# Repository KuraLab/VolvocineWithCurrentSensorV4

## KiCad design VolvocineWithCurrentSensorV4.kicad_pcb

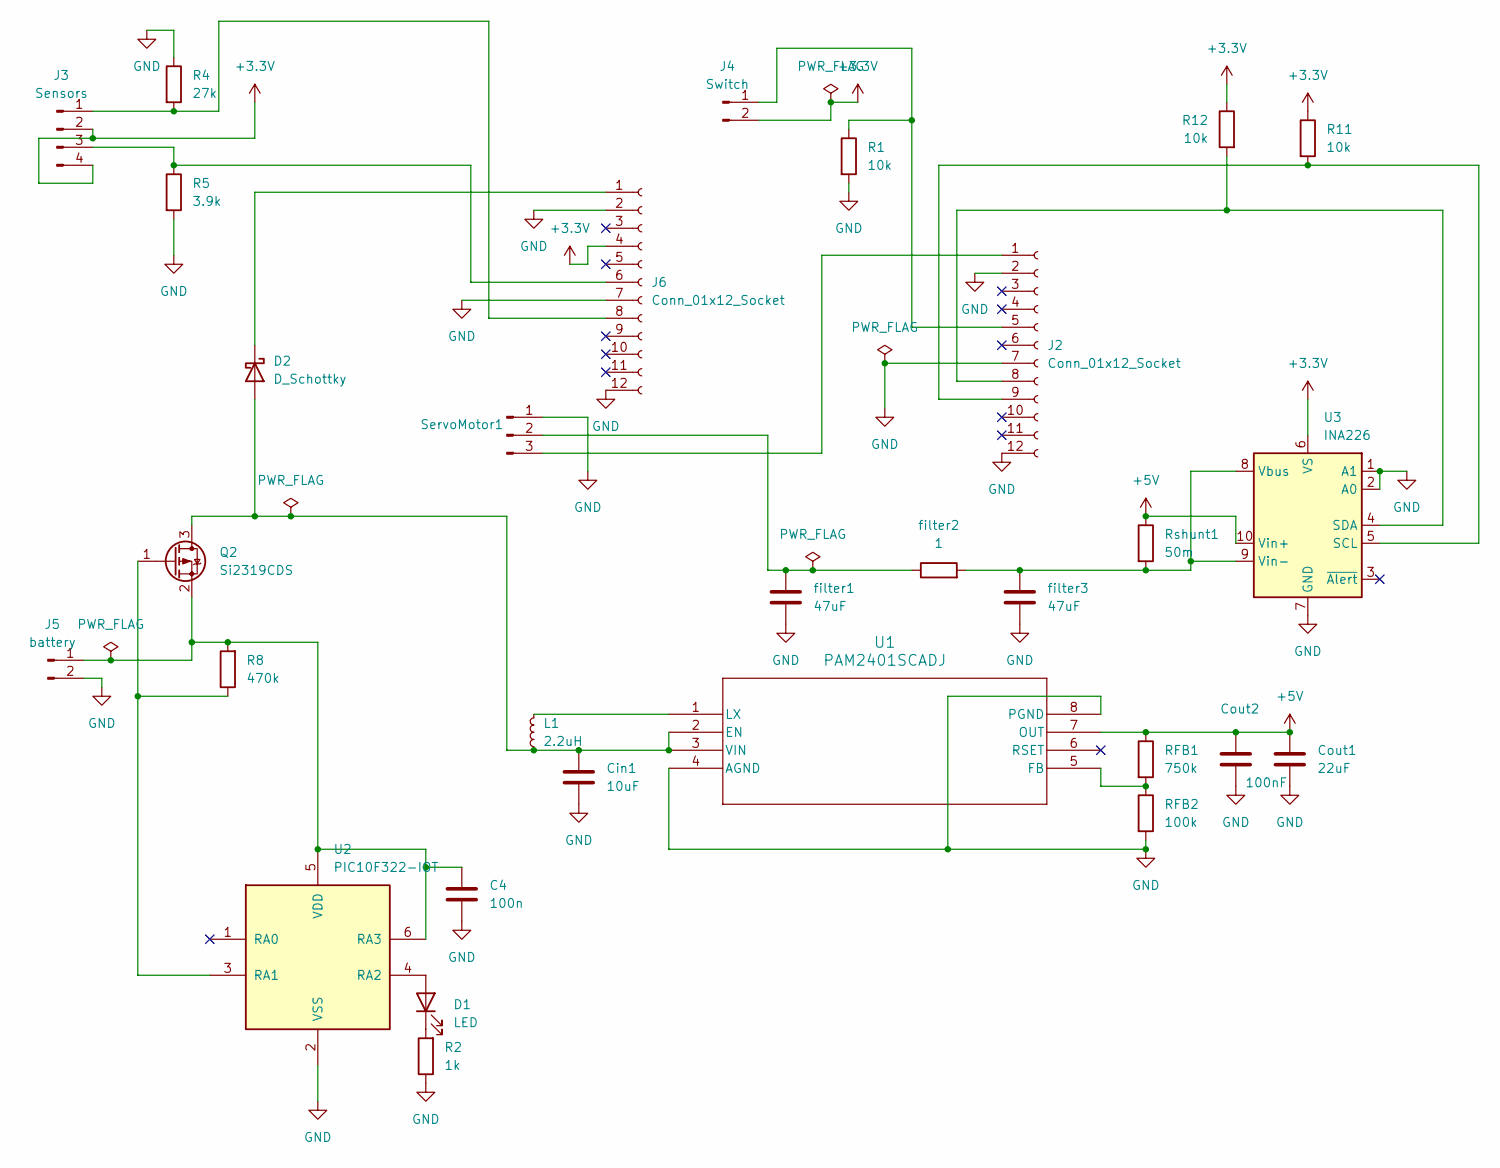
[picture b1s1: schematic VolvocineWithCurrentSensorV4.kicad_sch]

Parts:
C4: 100n; C_0603_1608Metric_Pad1.08x0.95mm_HandSolder
Cin1: 10uF; C_0603_1608Metric_Pad1.08x0.95mm_HandSolder
Cout1: 22uF; C_1206_3216Metric_Pad1.33x1.80mm_HandSolder
Cout2: 100nF; C_0603_1608Metric_Pad1.08x0.95mm_HandSolder
D1: LED; LED_0603_1608Metric_Pad1.05x0.95mm_HandSolder
D2: D_Schottky; D_SOD-128
J2, J6: Conn_01x12_Socket; PinSocket_1x12_P2.54mm_Vertical
J3: Sensors; PinHeader_1x04_P2.54mm_Vertical
J4: Switch; PinHeader_1x02_P2.54mm_Vertical
J5: battery; PinHeader_1x02_P2.54mm_Vertical
L1: 2.2uH; L_1008_2520Metric_Pad1.43x2.20mm_HandSolder
Q2: Si2319CDS; SOT-23
R1, R11, R12: 10k; R_0603_1608Metric_Pad0.98x0.95mm_HandSolder
R2: 1k; R_0603_1608Metric_Pad0.98x0.95mm_HandSolder
R4: 27k; R_0603_1608Metric_Pad0.98x0.95mm_HandSolder
R5: 3.9k; R_0603_1608Metric_Pad0.98x0.95mm_HandSolder
R8: 470k; R_0603_1608Metric_Pad0.98x0.95mm_HandSolder
RFB1: 750k; R_0603_1608Metric_Pad0.98x0.95mm_HandSolder
RFB2: 100k; R_0603_1608Metric_Pad0.98x0.95mm_HandSolder
Rshunt1: 50m; R_1206_3216Metric_Pad1.30x1.75mm_HandSolder
ServoMotor1: PinHeader_1x03_P2.54mm_Vertical
U1: PAM2401SCADJ; MSOP-8_3x3mm_P0.65mm
U2: PIC10F322-IOT; SOT-23-6
U3: INA226; VSSOP-10_3x3mm_P0.5mm
filter1, filter3: 47uF; C_1206_3216Metric_Pad1.33x1.80mm_HandSolder
filter2: 1; R_0603_1608Metric_Pad0.98x0.95mm_HandSolder

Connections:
+3.3V: J3.2, J3.4, J4.2, J6.4, R11.1, R12.1, U3.6 (VS)
+5V: Cout1.1, Cout2.1, RFB1.1, Rshunt1.1, U1.7 (OUT), U3.10 (Vin+)
GND: C4.2, Cin1.2, Cout1.2, Cout2.2, J2.2, J2.7, J2.12, J5.2, J6.2, J6.7, J6.12, R1.2, R2.1, R4.1, R5.2, RFB2.2, ServoMotor1.1, U1.4 (AGND), U1.8 (PGND), U2.2 (VSS), U3.1 (A1), U3.2 (A0), U3.7 (GND), filter1.2, filter3.2; also elsewhere on the board
unnamed: D1.2 (A), U2.4 (RA2)
unnamed: D1.1 (K), R2.2
unnamed: Cin1.1, D2.2 (A), L1.1, Q2.3 (D), U1.2 (EN), U1.3 (VIN)
unnamed: D2.1 (K), J6.1
unnamed 7: J2.1, ServoMotor1.3; also elsewhere on the board
unnamed: J2.5, J4.1, R1.1
unnamed: J2.8, R12.2, U3.4 (SDA)
unnamed: J2.9, R11.2, U3.5 (SCL)
unnamed: J3.1, J6.8, R4.2
unnamed: J3.3, J6.6, R5.1
unnamed: C4.1, J5.1, Q2.2 (S), R8.2, U2.5 (VDD), U2.6 (RA3)
unnamed: Q2.1 (G), R8.1, U2.3 (RA1)
unnamed 15: ServoMotor1.2, filter1.1, filter2.1; also elsewhere on the board
unnamed: RFB1.2, RFB2.1, U1.5 (FB)
unnamed: L1.2, U1.1 (LX)
unnamed: Rshunt1.2, U3.8 (Vbus), U3.9 (Vin-), filter2.2, filter3.1

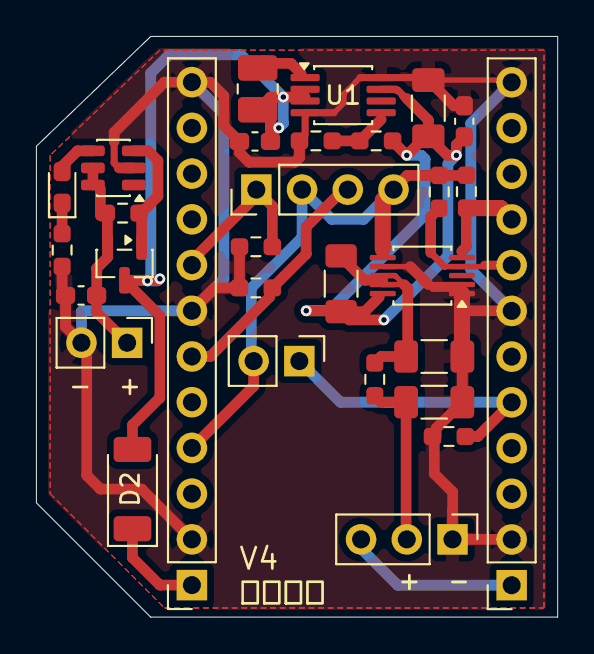
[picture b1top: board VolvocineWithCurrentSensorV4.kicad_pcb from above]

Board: 2 copper layers, 29.0 x 32.3 mm, 30 parts (0 on the bottom side), 19 nets.

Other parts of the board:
+  -: PinHeader_1x03_P2.54mm_Vertical

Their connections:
GND: + -.1; also elsewhere on the board
unnamed 7: + -.3; also elsewhere on the board
unnamed 15: + -.2; also elsewhere on the board

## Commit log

2026-04-22 Initial snapshot: 17 files changed ERC.rpt 27/0/0 ERC2.rpt 27/0/0 fp-lib-table 4/0/0 gerber_out/VolvocineWithCurrentSensorV4-B_Cu.gbr 2428/0/0 gerber_out/VolvocineWithCurrentSensorV4-B_Mask.gbr 76/0/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
2026-04-22 PCB Save: 3 files changed .gitignore 9/0/0 VolvocineWithCurrentSensorV4.kicad_pcb 84/0/433 VolvocineWithCurrentSensorV4.kicad_pro 33/0/4
2026-04-22 Autosave
2026-04-22 SCH Save: 2 files changed VolvocineWithCurrentSensorV4.kicad_pro 12/0/2 VolvocineWithCurrentSensorV4.kicad_sch 1058/0/519
2026-04-23 PCB Save: 2 files changed VolvocineWithCurrentSensorV4.kicad_pcb 0/0/986 VolvocineWithCurrentSensorV4.kicad_pro 0/0/1
2026-04-23 Remove obsolete Gerber and drill files for VolvocineWithCurrentSensorV4 project, including solder mask, silkscreen, NPTH, and PTH drill files, as well as the job file and symbol library table. This c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
2026-04-23 Add Gerber files and drill files for VolvocineWithCurrentSensorV4
    - Created new Gerber files for the top mask and silkscreen layers.
    - Added NPTH and PTH drill files for non-plated and plated holes.
    - Included a job file for the Gerber output with project specifications.
    - Updated the symbol library table with new component libraries.
2026-04-23 message
2026-04-23 Update component values in schematic and add backup files
